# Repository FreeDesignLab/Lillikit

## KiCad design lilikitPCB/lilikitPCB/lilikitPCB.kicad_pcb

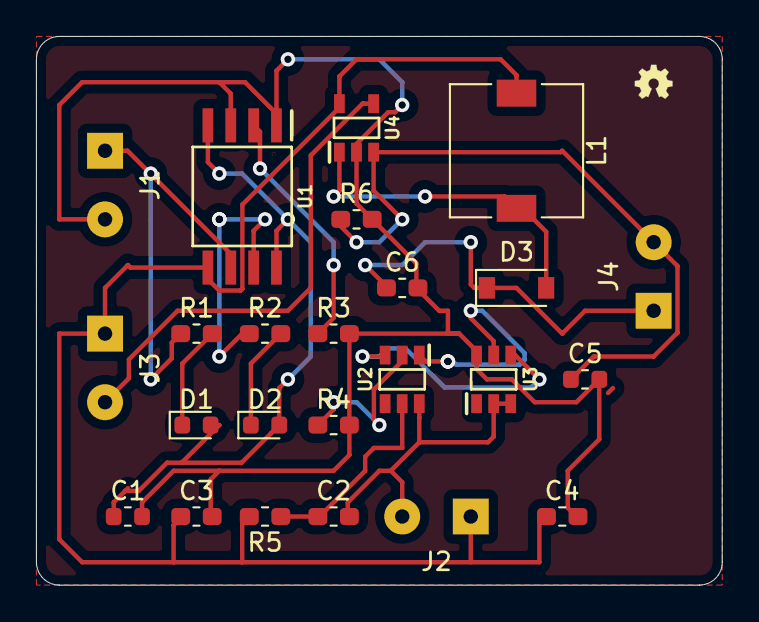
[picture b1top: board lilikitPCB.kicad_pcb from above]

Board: 2 copper layers, 38.1 x 30.5 mm, 24 parts (0 on the bottom side), 17 nets.

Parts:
C1: 4µ7; C_0603_1608Metric
C2: 0.1µF; C_0603_1608Metric_Pad1.05x0.95mm_HandSolder
C3: 10µF; C_0603_1608Metric_Pad1.05x0.95mm_HandSolder
C4: 4µ7F; C_0603_1608Metric_Pad1.05x0.95mm_HandSolder
C5: 1nF; C_0603_1608Metric
C6: 1µF; C_0603_1608Metric_Pad1.05x0.95mm_HandSolder
D1, D2: D; D_0603_1608Metric
D3: MBR0540; D_SOD-123
J1, J2, J3, J4: Conn_01x02; SolderWirePad_1x02_P3.81mm_Drill0.8mm
L1: 4µH; L_7.3x7.3_H4.5
R1, R2, R4: 1K; R_0603_1608Metric_Pad1.05x0.95mm_HandSolder
R3: 1.2K; R_0603_1608Metric_Pad1.05x0.95mm_HandSolder
R5: 100; R_0603_1608Metric_Pad1.05x0.95mm_HandSolder
R6: 68; R_0603_1608Metric_Pad1.05x0.95mm_HandSolder
U1: TP4056; SOP-8-208mil
U2: DW01A; SOT-23-6
U3: FS8205A-TSSOP-8; SOT-23-6
U4: LT1615; SOT-23-5

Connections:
unnamed: C1.1, D1.2, D2.2, U1.4, U1.8
unnamed: C1.2, C3.2, C4.2, C5.2, C6.2, J1.2, R3.2, R4.2, R6.2, U1.1, U1.3, U3.6, U4.2
unnamed: C2.1, R5.1, U2.5
unnamed: C2.2, J2.2, U2.6, U3.2, U3.3
unnamed: C3.1, C4.1, J2.1, J3.1, L1.1, R5.2, U1.5, U4.5
unnamed: C5.1, J4.2, R6.1, U4.3
unnamed: C6.1, D3.1, J4.1
unnamed: D1.1, R1.2
unnamed: D2.1, R2.2
unnamed: D3.2, L1.2, U4.1
unnamed: J1.1, R1.1, U1.6
unnamed: J3.2, U4.4
unnamed: R2.1, U1.7
unnamed: R3.1, U1.2
unnamed: R4.1, U2.2
unnamed: U2.1, U3.5
unnamed: U2.3, U3.4

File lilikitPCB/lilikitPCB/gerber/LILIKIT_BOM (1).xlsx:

Item | Quantity | Part | Reference | Package | ManPartNo | Supplier
1.0 | 1.0 | G |  | A
2.0 | 1.0 | D3 | MBR0540 | D_SOD-123
3.0 | 4.0 | J1,J2,J3,J4 | Conn_01x02 | SolderWirePad_1x02_P3.81mm_Drill0.8mm
4.0 | 1.0 | L1 | 4µH | L_7.3x7.3_H4.5
5.0 | 3.0 | R1,R2,R4 | 1K | R_0603_1608Metric_Pad1.05x0.95mm_HandSolder
6.0 | 1.0 | R3 | 1,2K | R_0603_1608Metric_Pad1.05x0.95mm_HandSolder
7.0 | 1.0 | R5 | 100.0 | "R_0603_1608Metric_Pad1.05x0.95mm_HandSolder
8.0 | 1.0 | R6 | 68.0 | "R_0603_1608Metric_Pad1.05x0.95mm_HandSolder
9.0 | 1.0 | U1 | TP4056 | SOP-8-208mil
10.0 | 1.0 | U2 | DW01A | SOT-23-6
11.0 | 1.0 | U3 | FS8205A-TSSOP-8 | SOT-23-6
12.0 | 1.0 | U4 | LT1615 | SOT-23-5
13.0 | 1.0 | C1 | 4µ7 | C_0603_1608Metric
14.0 | 1.0 | C2 | 0.1µF | C_0603_1608Metric_Pad1.05x0.95mm_HandSolder
15.0 | 1.0 | C3 | 10µF | C_0603_1608Metric_Pad1.05x0.95mm_HandSolder
16.0 | 1.0 | C4 | 4µ7F | C_0603_1608Metric_Pad1.05x0.95mm_HandSolder
17.0 | 1.0 | C5 | 1nF | C_0603_1608Metric
18.0 | 1.0 | C6 | 1µF | C_0603_1608Metric_Pad1.05x0.95mm_HandSolder
19.0 | 2.0 | D1(red),D2(green) | D | D_0603_1608Metric

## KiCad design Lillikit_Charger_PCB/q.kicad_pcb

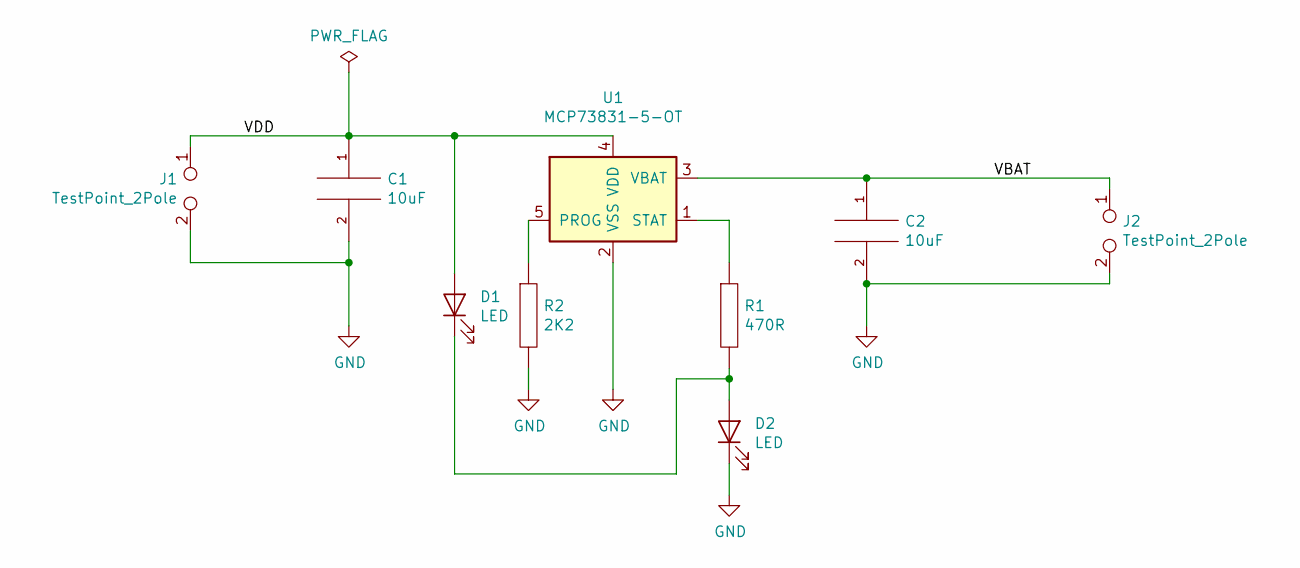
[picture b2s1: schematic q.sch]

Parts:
C1, C2: 10uF; C_0805_2012Metric
D1, D2: LED; LED_0402_1005Metric
J1, J2: TestPoint_2Pole; TestPoint_2Pads_Pitch2.54mm_Drill0.8mm
R1: 470R; R_0402_1005Metric
R2: 2K2; R_0402_1005Metric
U1: MCP73831-5-OT; SOT-23-5_HandSoldering

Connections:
/VBAT: C2.1, J2.1, U1.3 (VBAT)
/VDD: C1.1, D1.2 (A), J1.1, U1.4 (VDD)
GND: C1.2, C2.2, D2.1 (K), J1.2, J2.2, R2.2, U1.2 (VSS)
unnamed: D1.1 (K), D2.2 (A), R1.2
unnamed: R1.1, U1.1 (STAT)
unnamed: R2.1, U1.5 (PROG)

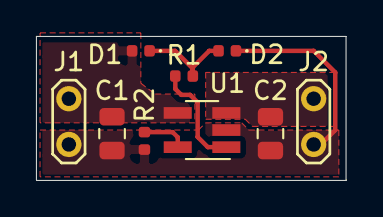
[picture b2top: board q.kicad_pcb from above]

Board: 2 copper layers, 17.2 x 8.0 mm, 9 parts (0 on the bottom side), 6 nets.

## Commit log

2019-07-17 Create LICENSE
